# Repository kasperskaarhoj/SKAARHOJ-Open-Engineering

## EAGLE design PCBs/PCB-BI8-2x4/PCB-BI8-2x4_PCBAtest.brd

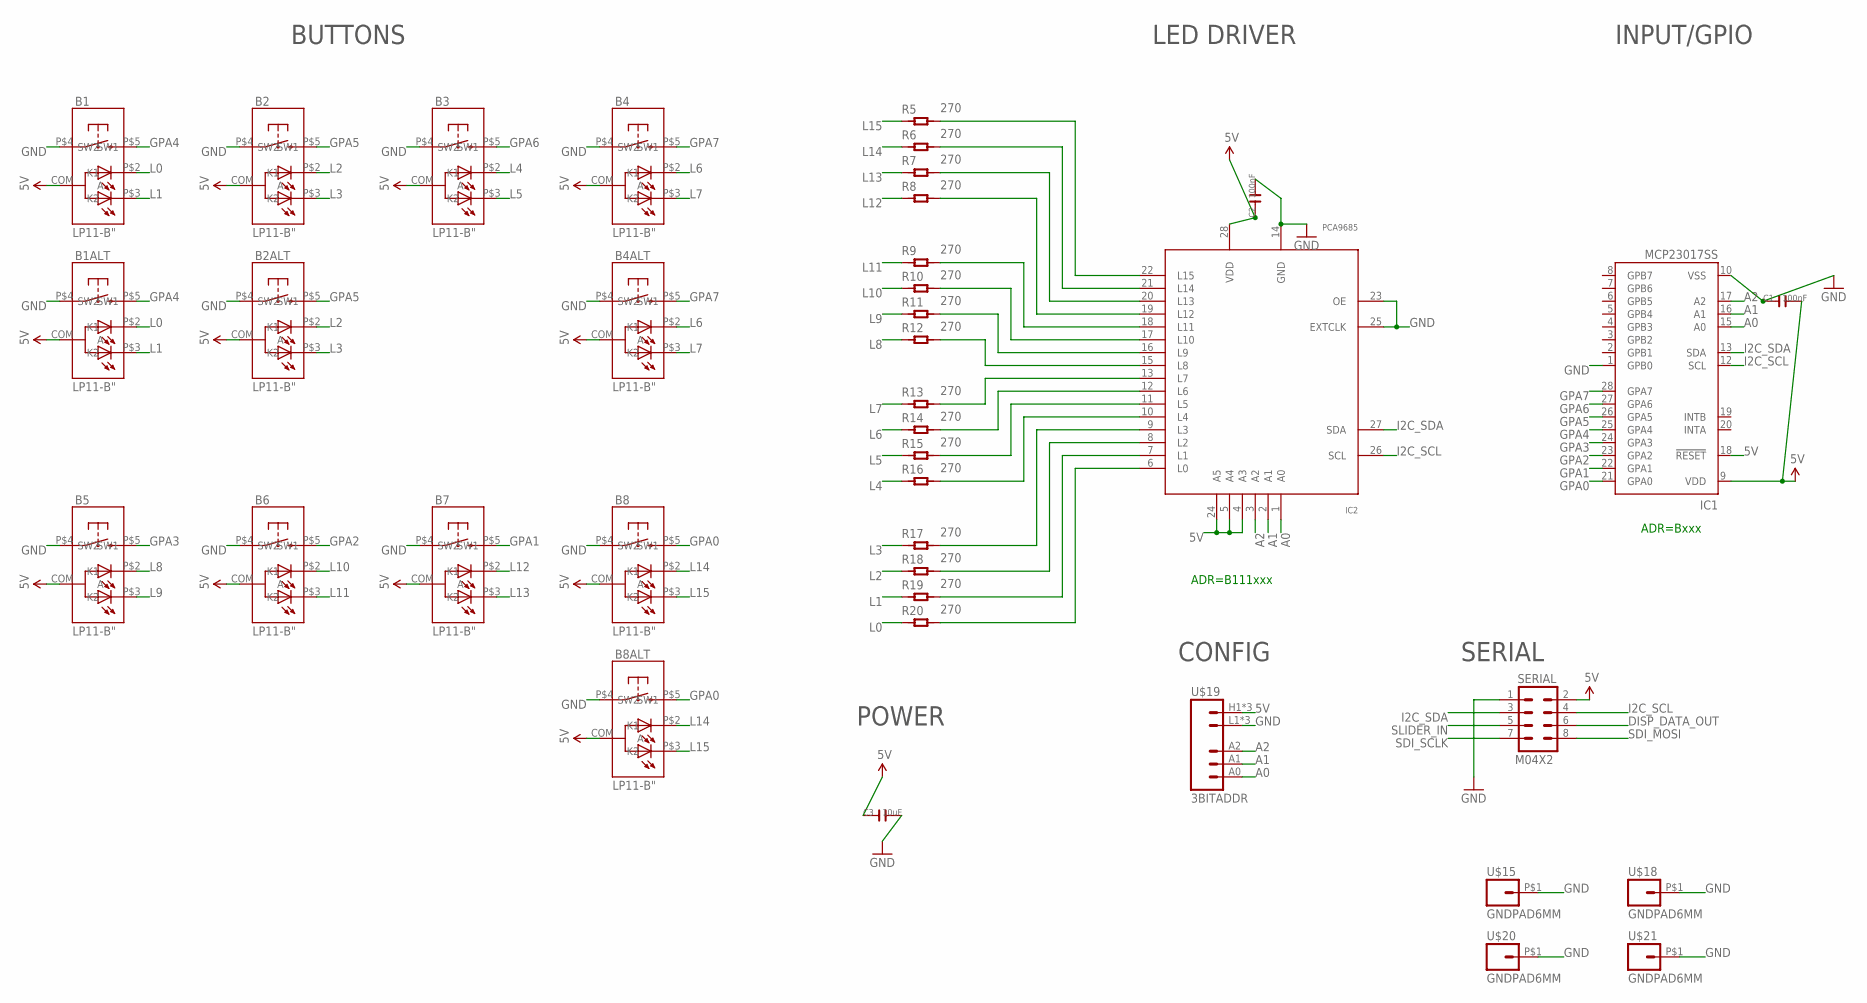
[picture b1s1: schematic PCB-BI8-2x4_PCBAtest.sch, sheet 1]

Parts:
B1, B1ALT, B2, B2ALT, B3, B4, B4ALT, B5, B6, B7, B8, B8ALT: LP11-B"; LP11
C1, C2: 100nF; C0603
C3: 10uF; C0805
IC1: MCP23017SS; SSOP28; MPN MCP23017-E/SS
IC2: PCA9685; TSSOP28
R5, R6, R7, R8, R9, R10, R11, R12, R13, R14, R15, R16, R17, R18, R19, R20: 270; R0603
SERIAL: M04X2; 2X4
U$15, U$18, U$20, U$21: GNDPAD6MM; 3.2MMPAD6MM
U$19: 3BITADDR

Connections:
5V: B1.COM (A), B1ALT.COM (A), B2.COM (A), B2ALT.COM (A), B3.COM (A), B4.COM (A), B4ALT.COM (A), B5.COM (A), B6.COM (A), B7.COM (A), B8.COM (A), B8ALT.COM (A), C1.2, C2.1, C3.1, IC1.9 (VDD), IC1.18 (!RESET), IC2.4 (A3), IC2.5 (A4), IC2.24 (A5), IC2.28 (VDD), SERIAL.2, U$19.H1 (VCC), U$19.H2 (VCC), U$19.H3 (VCC)
A0: IC1.15 (A0), IC2.1 (A0), U$19.A0
A1: IC1.16 (A1), IC2.2 (A1), U$19.A1
A2: IC1.17 (A2), IC2.3 (A2), U$19.A2
DISP_DATA_OUT: SERIAL.6
GND: B1.P$4 (SW1), B1ALT.P$4 (SW1), B2.P$4 (SW1), B2ALT.P$4 (SW1), B3.P$4 (SW1), B4.P$4 (SW1), B4ALT.P$4 (SW1), B5.P$4 (SW1), B6.P$4 (SW1), B7.P$4 (SW1), B8.P$4 (SW1), B8ALT.P$4 (SW1), C1.1, C2.2, C3.2, IC1.1 (GPB0), IC1.10 (VSS), IC2.14 (GND), IC2.23 (OE), IC2.25 (EXTCLK), SERIAL.1, U$15.P$1, U$18.P$1, U$19.L1 (GND), U$19.L2 (GND), U$19.L3 (GND), U$20.P$1, U$21.P$1
GPA0: B8.P$5 (SW2), B8ALT.P$5 (SW2), IC1.21 (GPA0)
GPA1: B7.P$5 (SW2), IC1.22 (GPA1)
GPA2: B6.P$5 (SW2), IC1.23 (GPA2)
GPA3: B5.P$5 (SW2), IC1.24 (GPA3)
GPA4: B1.P$5 (SW2), B1ALT.P$5 (SW2), IC1.25 (GPA4)
GPA5: B2.P$5 (SW2), B2ALT.P$5 (SW2), IC1.26 (GPA5)
GPA6: B3.P$5 (SW2), IC1.27 (GPA6)
GPA7: B4.P$5 (SW2), B4ALT.P$5 (SW2), IC1.28 (GPA7)
I2C_SCL: IC1.12 (SCL), IC2.26 (SCL), SERIAL.4
I2C_SDA: IC1.13 (SDA), IC2.27 (SDA), SERIAL.3
L0: B1.P$2 (K1), B1ALT.P$2 (K1), R20.1
L1: B1.P$3 (K2), B1ALT.P$3 (K2), R19.1
L2: B2.P$2 (K1), B2ALT.P$2 (K1), R18.1
L3: B2.P$3 (K2), B2ALT.P$3 (K2), R17.1
L4: B3.P$2 (K1), R16.1
L5: B3.P$3 (K2), R15.1
L6: B4.P$2 (K1), B4ALT.P$2 (K1), R14.1
L7: B4.P$3 (K2), B4ALT.P$3 (K2), R13.1
L8: B5.P$2 (K1), R12.1
L9: B5.P$3 (K2), R11.1
L10: B6.P$2 (K1), R10.1
L11: B6.P$3 (K2), R9.1
L12: B7.P$2 (K1), R8.1
L13: B7.P$3 (K2), R7.1
L14: B8.P$2 (K1), B8ALT.P$2 (K1), R6.1
L15: B8.P$3 (K2), B8ALT.P$3 (K2), R5.1
unnamed: IC2.13 (L7), R13.2
unnamed: IC2.12 (L6), R14.2
unnamed: IC2.11 (L5), R15.2
unnamed: IC2.10 (L4), R16.2
unnamed: IC2.9 (L3), R17.2
unnamed: IC2.8 (L2), R18.2
unnamed: IC2.7 (L1), R19.2
unnamed: IC2.6 (L0), R20.2
unnamed: IC2.15 (L8), R12.2
unnamed: IC2.16 (L9), R11.2
unnamed: IC2.17 (L10), R10.2
unnamed: IC2.18 (L11), R9.2
unnamed: IC2.19 (L12), R8.2
unnamed: IC2.20 (L13), R7.2
unnamed: IC2.21 (L14), R6.2
unnamed: IC2.22 (L15), R5.2
SDI_MOSI: SERIAL.8
SDI_SCLK: SERIAL.7
SLIDER_IN: SERIAL.5

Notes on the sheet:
ADR=B111xxx
ADR=Bxxx
BUTTONS
LED DRIVER
INPUT/GPIO
POWER
SERIAL
CONFIG

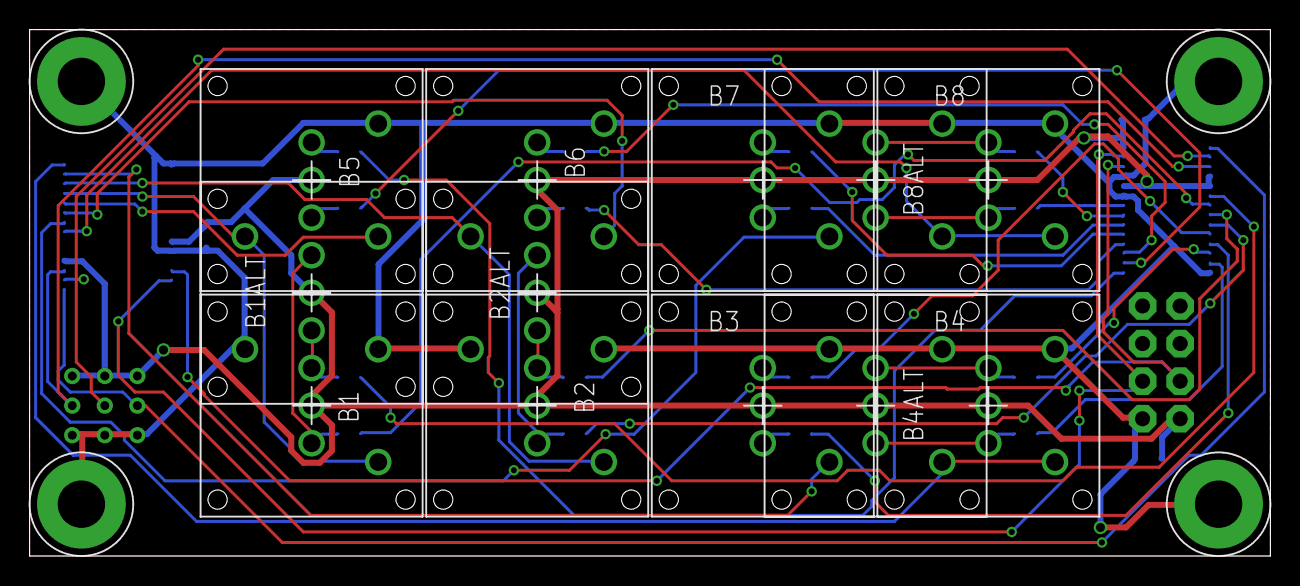
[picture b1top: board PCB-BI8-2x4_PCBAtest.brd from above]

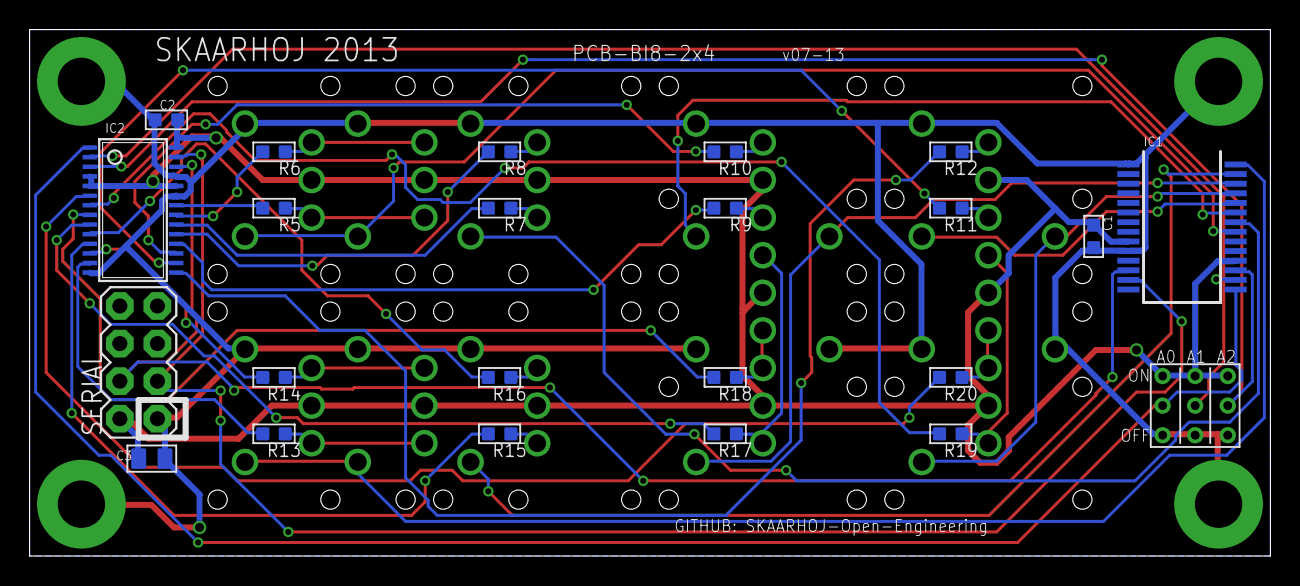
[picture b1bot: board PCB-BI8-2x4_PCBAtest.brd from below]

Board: 2 copper layers, 83.8 x 35.6 mm, 39 parts (23 on the bottom side), 47 nets.

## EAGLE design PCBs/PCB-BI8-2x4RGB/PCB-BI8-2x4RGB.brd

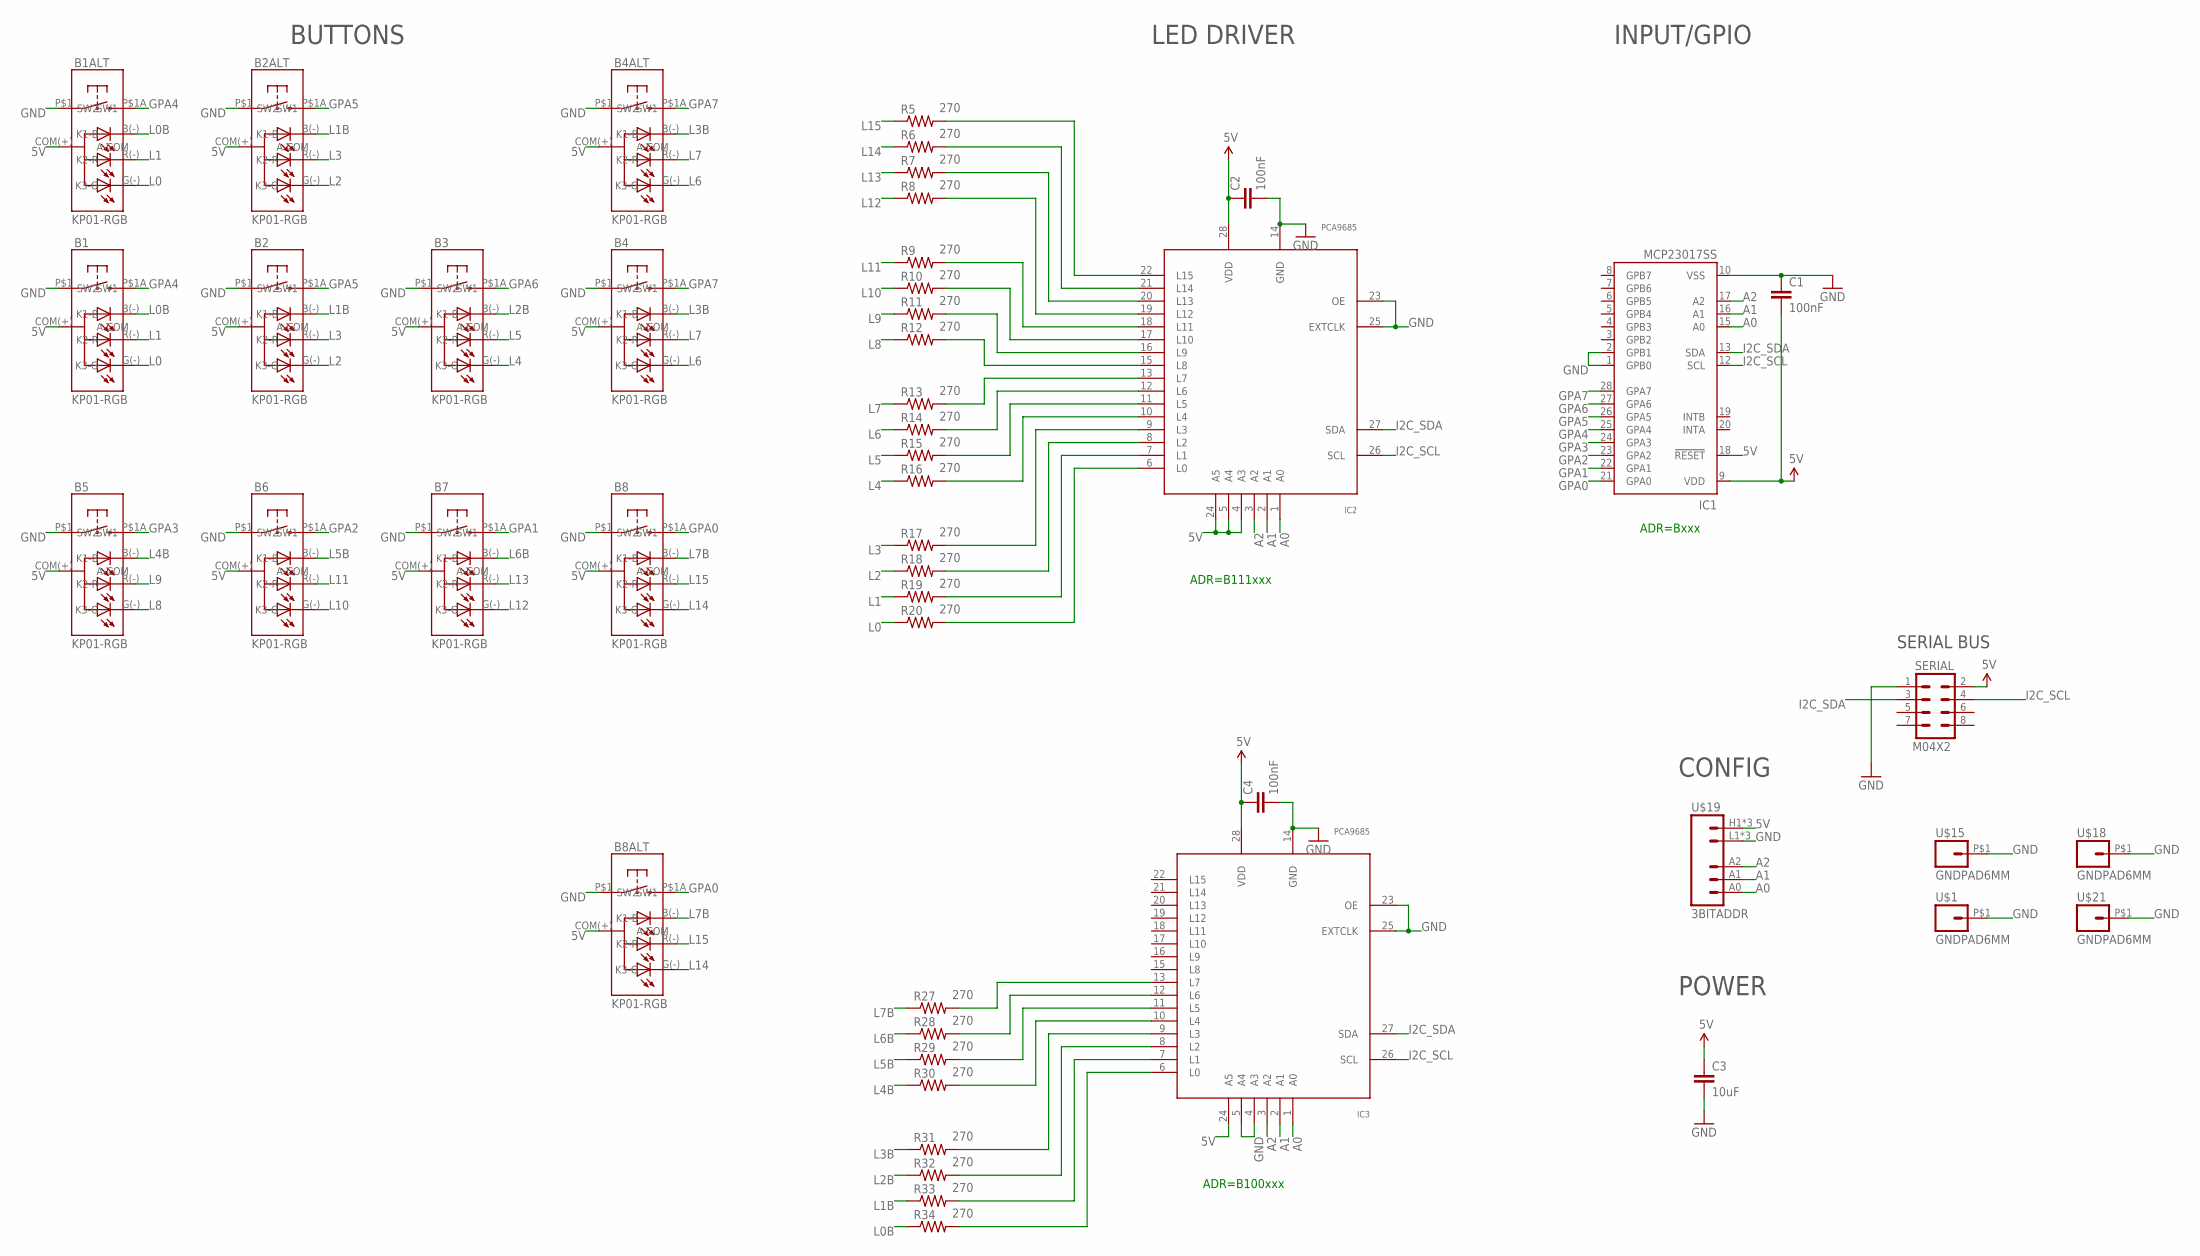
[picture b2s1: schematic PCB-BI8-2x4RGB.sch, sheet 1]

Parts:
B1, B1ALT, B2, B2ALT, B3, B4, B4ALT, B5, B6, B7, B8, B8ALT: KP01-RGB; NKK-KP01
C1, C2, C4: 100nF; 0603-CAP
C3: 10uF; 0805
IC1: MCP23017SS; SSOP28; MPN MCP23017-E/SS
IC2, IC3: PCA9685; TSSOP28
R5, R6, R7, R8, R9, R10, R11, R12, R13, R14, R15, R16, R17, R18, R19, R20, R27, R28, R29, R30, R31, R32, R33, R34: 270; 0603-RES
SERIAL: M04X2; 2X4
U$1, U$15, U$18, U$21: GNDPAD6MM; 3.2MMPAD6MM
U$19: 3BITADDR

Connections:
5V: B1.COM(+) (A-COM), B1ALT.COM(+) (A-COM), B2.COM(+) (A-COM), B2ALT.COM(+) (A-COM), B3.COM(+) (A-COM), B4.COM(+) (A-COM), B4ALT.COM(+) (A-COM), B5.COM(+) (A-COM), B6.COM(+) (A-COM), B7.COM(+) (A-COM), B8.COM(+) (A-COM), B8ALT.COM(+) (A-COM), C1.2, C2.1, C3.1, C4.1, IC1.9 (VDD), IC1.18 (!RESET), IC2.4 (A3), IC2.5 (A4), IC2.24 (A5), IC2.28 (VDD), IC3.24 (A5), IC3.28 (VDD), SERIAL.2, U$19.H1 (VCC), U$19.H2 (VCC), U$19.H3 (VCC)
A0: IC1.15 (A0), IC2.1 (A0), IC3.1 (A0), U$19.A0
A1: IC1.16 (A1), IC2.2 (A1), IC3.2 (A1), U$19.A1
A2: IC1.17 (A2), IC2.3 (A2), IC3.3 (A2), U$19.A2
GND: B1.P$1 (SW1), B1ALT.P$1 (SW1), B2.P$1 (SW1), B2ALT.P$1 (SW1), B3.P$1 (SW1), B4.P$1 (SW1), B4ALT.P$1 (SW1), B5.P$1 (SW1), B6.P$1 (SW1), B7.P$1 (SW1), B8.P$1 (SW1), B8ALT.P$1 (SW1), C1.1, C2.2, C3.2, C4.2, IC1.1 (GPB0), IC1.2 (GPB1), IC1.10 (VSS), IC2.14 (GND), IC2.23 (OE), IC2.25 (EXTCLK), IC3.4 (A3), IC3.5 (A4), IC3.14 (GND), IC3.23 (OE), IC3.25 (EXTCLK), SERIAL.1, U$1.P$1, U$15.P$1, U$18.P$1, U$19.L1 (GND), U$19.L2 (GND), U$19.L3 (GND), U$21.P$1
GPA0: B8.P$1A (SW2), B8ALT.P$1A (SW2), IC1.21 (GPA0)
GPA1: B7.P$1A (SW2), IC1.22 (GPA1)
GPA2: B6.P$1A (SW2), IC1.23 (GPA2)
GPA3: B5.P$1A (SW2), IC1.24 (GPA3)
GPA4: B1.P$1A (SW2), B1ALT.P$1A (SW2), IC1.25 (GPA4)
GPA5: B2.P$1A (SW2), B2ALT.P$1A (SW2), IC1.26 (GPA5)
GPA6: B3.P$1A (SW2), IC1.27 (GPA6)
GPA7: B4.P$1A (SW2), B4ALT.P$1A (SW2), IC1.28 (GPA7)
I2C_SCL: IC1.12 (SCL), IC2.26 (SCL), IC3.26 (SCL), SERIAL.4
I2C_SDA: IC1.13 (SDA), IC2.27 (SDA), IC3.27 (SDA), SERIAL.3
L0: B1.G(-) (K3-G), B1ALT.G(-) (K3-G), R20.1
L0B: B1.B(-) (K1-B), B1ALT.B(-) (K1-B), R34.1
L1: B1.R(-) (K2-R), B1ALT.R(-) (K2-R), R19.1
L1B: B2.B(-) (K1-B), B2ALT.B(-) (K1-B), R33.1
L2: B2.G(-) (K3-G), B2ALT.G(-) (K3-G), R18.1
L2B: B3.B(-) (K1-B), R32.1
L3: B2.R(-) (K2-R), B2ALT.R(-) (K2-R), R17.1
L3B: B4.B(-) (K1-B), B4ALT.B(-) (K1-B), R31.1
L4: B3.G(-) (K3-G), R16.1
L4B: B5.B(-) (K1-B), R30.1
L5: B3.R(-) (K2-R), R15.1
L5B: B6.B(-) (K1-B), R29.1
L6: B4.G(-) (K3-G), B4ALT.G(-) (K3-G), R14.1
L6B: B7.B(-) (K1-B), R28.1
L7: B4.R(-) (K2-R), B4ALT.R(-) (K2-R), R13.1
L7B: B8.B(-) (K1-B), B8ALT.B(-) (K1-B), R27.1
L8: B5.G(-) (K3-G), R12.1
L9: B5.R(-) (K2-R), R11.1
L10: B6.G(-) (K3-G), R10.1
L11: B6.R(-) (K2-R), R9.1
L12: B7.G(-) (K3-G), R8.1
L13: B7.R(-) (K2-R), R7.1
L14: B8.G(-) (K3-G), B8ALT.G(-) (K3-G), R6.1
L15: B8.R(-) (K2-R), B8ALT.R(-) (K2-R), R5.1
unnamed: IC3.13 (L7), R27.2
unnamed: IC3.12 (L6), R28.2
unnamed: IC2.13 (L7), R13.2
unnamed: IC2.12 (L6), R14.2
unnamed: IC3.11 (L5), R29.2
unnamed: IC2.11 (L5), R15.2
unnamed: IC2.10 (L4), R16.2
unnamed: IC2.9 (L3), R17.2
unnamed: IC2.8 (L2), R18.2
unnamed: IC2.7 (L1), R19.2
unnamed: IC3.10 (L4), R30.2
unnamed: IC3.9 (L3), R31.2
unnamed: IC3.8 (L2), R32.2
unnamed: IC3.7 (L1), R33.2
unnamed: IC3.6 (L0), R34.2
unnamed: IC2.6 (L0), R20.2
unnamed: IC2.15 (L8), R12.2
unnamed: IC2.16 (L9), R11.2
unnamed: IC2.17 (L10), R10.2
unnamed: IC2.18 (L11), R9.2
unnamed: IC2.19 (L12), R8.2
unnamed: IC2.20 (L13), R7.2
unnamed: IC2.21 (L14), R6.2
unnamed: IC2.22 (L15), R5.2

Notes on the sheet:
SERIAL BUS
ADR=B111xxx
ADR=Bxxx
BUTTONS
LED DRIVER
INPUT/GPIO
POWER
ADR=B100xxx
CONFIG

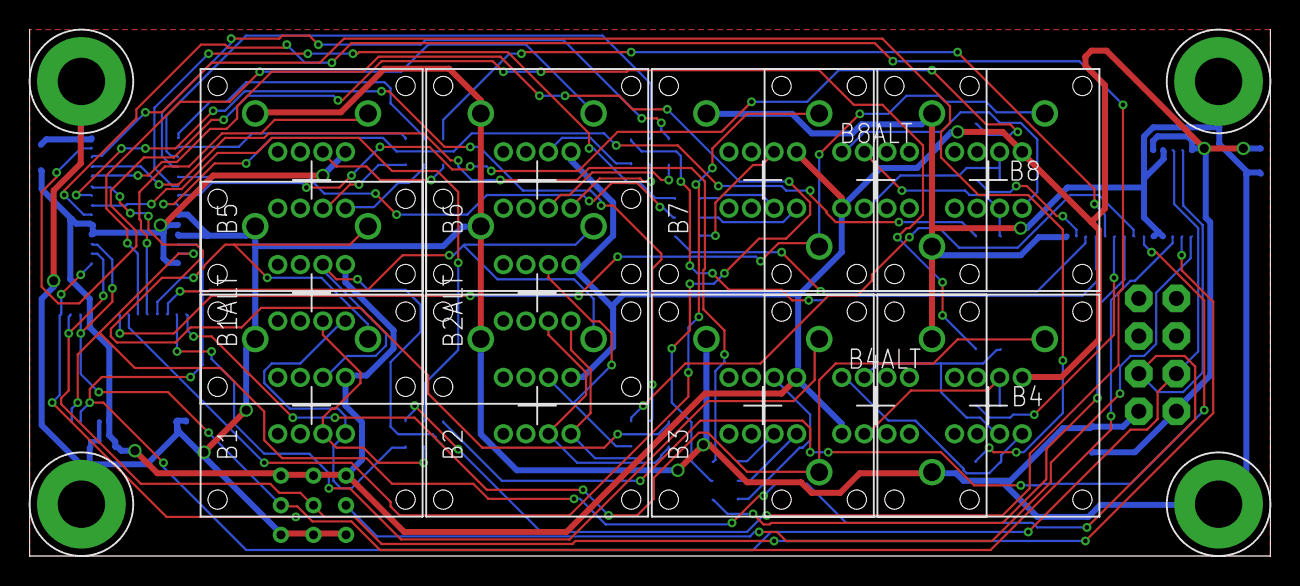
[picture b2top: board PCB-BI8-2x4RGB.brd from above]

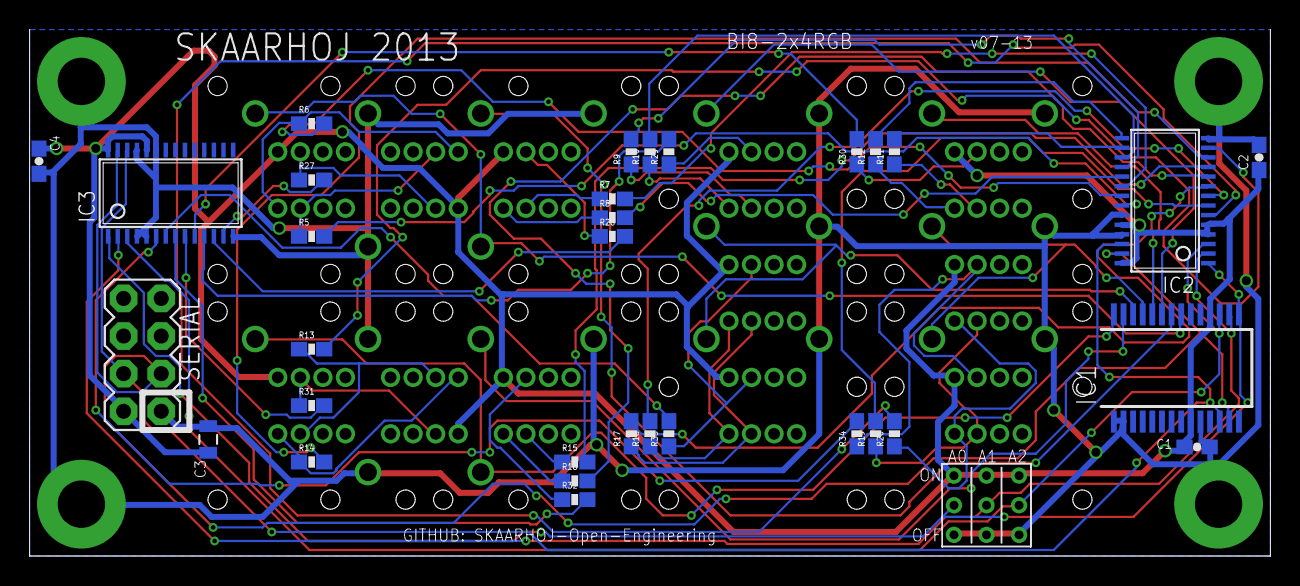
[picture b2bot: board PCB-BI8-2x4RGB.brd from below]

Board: 2 copper layers, 83.8 x 35.6 mm, 49 parts (33 on the bottom side), 63 nets.

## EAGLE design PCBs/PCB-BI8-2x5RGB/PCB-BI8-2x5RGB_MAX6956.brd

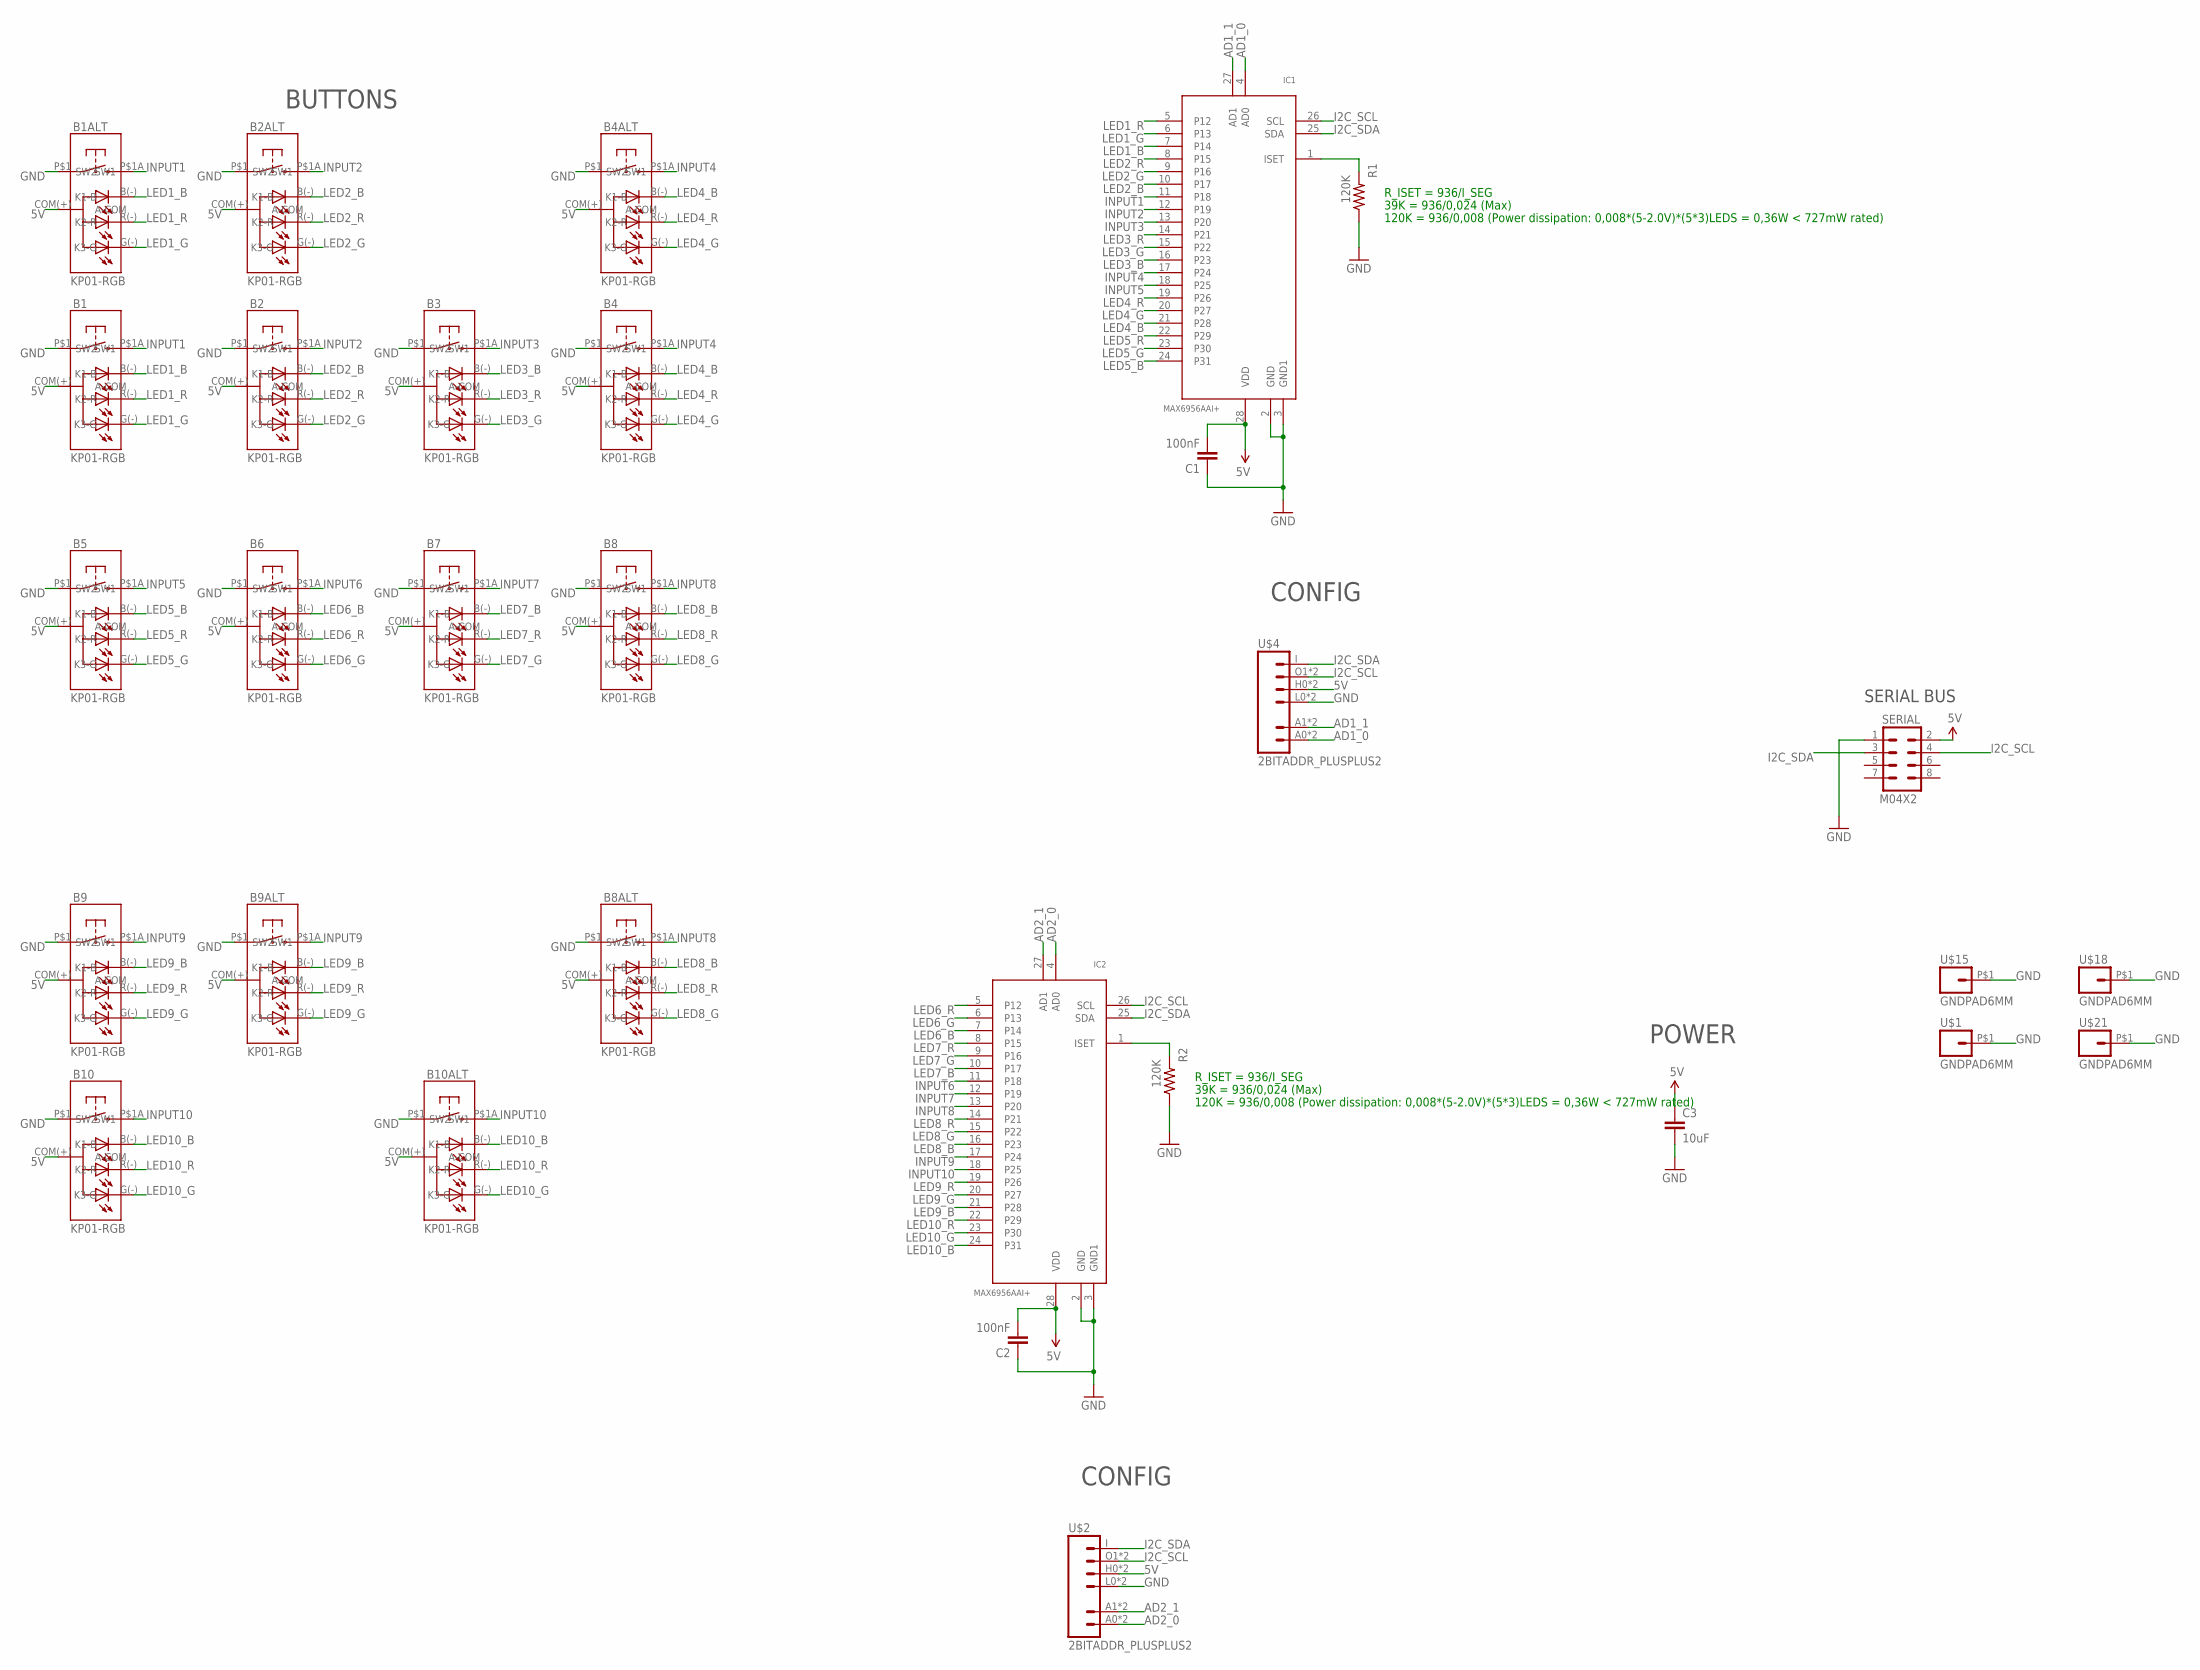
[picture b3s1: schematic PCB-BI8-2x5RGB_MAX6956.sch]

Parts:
B1, B1ALT, B2, B2ALT, B3, B4, B4ALT, B5, B6, B7, B8, B8ALT, B9, B9ALT, B10, B10ALT: KP01-RGB; NKK-KP01
C1, C2: 100nF; 0603-CAP
C3: 10uF; 0805
IC1, IC2: MAX6956AAI+; SSOP28
R1, R2: 120K; 0603-RES
SERIAL: M04X2; 2X4
U$1, U$15, U$18, U$21: GNDPAD6MM; 3.2MMPAD6MM
U$2, U$4: 2BITADDR_PLUSPLUS2; 2BITADDR_SMALL_PLUS2

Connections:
5V: B1.COM(+) (A-COM), B1ALT.COM(+) (A-COM), B2.COM(+) (A-COM), B2ALT.COM(+) (A-COM), B3.COM(+) (A-COM), B4.COM(+) (A-COM), B4ALT.COM(+) (A-COM), B5.COM(+) (A-COM), B6.COM(+) (A-COM), B7.COM(+) (A-COM), B8.COM(+) (A-COM), B8ALT.COM(+) (A-COM), B9.COM(+) (A-COM), B9ALT.COM(+) (A-COM), B10.COM(+) (A-COM), B10ALT.COM(+) (A-COM), C1.2, C2.2, C3.1, IC1.28 (VDD), IC2.28 (VDD), SERIAL.2, U$2.H0 (VCC), U$2.H1 (VCC), U$4.H0 (VCC), U$4.H1 (VCC)
AD1_0: IC1.4 (AD0), U$4.A0 (A1), U$4.AS0 (A1)
AD1_1: IC1.27 (AD1), U$4.A1 (A2), U$4.AS1 (A2)
AD2_0: IC2.4 (AD0), U$2.A0 (A1), U$2.AS0 (A1)
AD2_1: IC2.27 (AD1), U$2.A1 (A2), U$2.AS1 (A2)
GND: B1.P$1 (SW1), B1ALT.P$1 (SW1), B2.P$1 (SW1), B2ALT.P$1 (SW1), B3.P$1 (SW1), B4.P$1 (SW1), B4ALT.P$1 (SW1), B5.P$1 (SW1), B6.P$1 (SW1), B7.P$1 (SW1), B8.P$1 (SW1), B8ALT.P$1 (SW1), B9.P$1 (SW1), B9ALT.P$1 (SW1), B10.P$1 (SW1), B10ALT.P$1 (SW1), C1.1, C2.1, C3.2, IC1.2 (GND), IC1.3 (GND1), IC2.2 (GND), IC2.3 (GND1), R1.1, R2.1, SERIAL.1, U$1.P$1, U$2.L0 (GND), U$2.L1 (GND), U$4.L0 (GND), U$4.L1 (GND), U$15.P$1, U$18.P$1, U$21.P$1
I2C_SCL: IC1.26 (SCL), IC2.26 (SCL), SERIAL.4, U$2.O1 (3), U$2.O2 (3), U$4.O1 (3), U$4.O2 (3)
I2C_SDA: IC1.25 (SDA), IC2.25 (SDA), SERIAL.3, U$2.I (4), U$4.I (4)
INPUT1: B1.P$1A (SW2), B1ALT.P$1A (SW2), IC1.11 (P18)
INPUT2: B2.P$1A (SW2), B2ALT.P$1A (SW2), IC1.12 (P19)
INPUT3: B3.P$1A (SW2), IC1.13 (P20)
INPUT4: B4.P$1A (SW2), B4ALT.P$1A (SW2), IC1.17 (P24)
INPUT5: B5.P$1A (SW2), IC1.18 (P25)
INPUT6: B6.P$1A (SW2), IC2.11 (P18)
INPUT7: B7.P$1A (SW2), IC2.12 (P19)
INPUT8: B8.P$1A (SW2), B8ALT.P$1A (SW2), IC2.13 (P20)
INPUT9: B9.P$1A (SW2), B9ALT.P$1A (SW2), IC2.17 (P24)
INPUT10: B10.P$1A (SW2), B10ALT.P$1A (SW2), IC2.18 (P25)
LED1_B: B1.B(-) (K1-B), B1ALT.B(-) (K1-B), IC1.7 (P14)
LED1_G: B1.G(-) (K3-G), B1ALT.G(-) (K3-G), IC1.6 (P13)
LED1_R: B1.R(-) (K2-R), B1ALT.R(-) (K2-R), IC1.5 (P12)
LED2_B: B2.B(-) (K1-B), B2ALT.B(-) (K1-B), IC1.10 (P17)
LED2_G: B2.G(-) (K3-G), B2ALT.G(-) (K3-G), IC1.9 (P16)
LED2_R: B2.R(-) (K2-R), B2ALT.R(-) (K2-R), IC1.8 (P15)
LED3_B: B3.B(-) (K1-B), IC1.16 (P23)
LED3_G: B3.G(-) (K3-G), IC1.15 (P22)
LED3_R: B3.R(-) (K2-R), IC1.14 (P21)
LED4_B: B4.B(-) (K1-B), B4ALT.B(-) (K1-B), IC1.21 (P28)
LED4_G: B4.G(-) (K3-G), B4ALT.G(-) (K3-G), IC1.20 (P27)
LED4_R: B4.R(-) (K2-R), B4ALT.R(-) (K2-R), IC1.19 (P26)
LED5_B: B5.B(-) (K1-B), IC1.24 (P31)
LED5_G: B5.G(-) (K3-G), IC1.23 (P30)
LED5_R: B5.R(-) (K2-R), IC1.22 (P29)
LED6_B: B6.B(-) (K1-B), IC2.7 (P14)
LED6_G: B6.G(-) (K3-G), IC2.6 (P13)
LED6_R: B6.R(-) (K2-R), IC2.5 (P12)
LED7_B: B7.B(-) (K1-B), IC2.10 (P17)
LED7_G: B7.G(-) (K3-G), IC2.9 (P16)
LED7_R: B7.R(-) (K2-R), IC2.8 (P15)
LED8_B: B8.B(-) (K1-B), B8ALT.B(-) (K1-B), IC2.16 (P23)
LED8_G: B8.G(-) (K3-G), B8ALT.G(-) (K3-G), IC2.15 (P22)
LED8_R: B8.R(-) (K2-R), B8ALT.R(-) (K2-R), IC2.14 (P21)
LED9_B: B9.B(-) (K1-B), B9ALT.B(-) (K1-B), IC2.21 (P28)
LED9_G: B9.G(-) (K3-G), B9ALT.G(-) (K3-G), IC2.20 (P27)
LED9_R: B9.R(-) (K2-R), B9ALT.R(-) (K2-R), IC2.19 (P26)
LED10_B: B10.B(-) (K1-B), B10ALT.B(-) (K1-B), IC2.24 (P31)
LED10_G: B10.G(-) (K3-G), B10ALT.G(-) (K3-G), IC2.23 (P30)
LED10_R: B10.R(-) (K2-R), B10ALT.R(-) (K2-R), IC2.22 (P29)
unnamed: IC2.1 (ISET), R2.2
unnamed: IC1.1 (ISET), R1.2

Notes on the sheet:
SERIAL BUS
BUTTONS
POWER
CONFIG
R_ISET = 936/I_SEG
39K = 936/0,024 (Max)
120K = 936/0,008 (Power dissipation: 0,008*(5-2.0V)*(5*3)LEDS = 0,36W < 727mW rated)

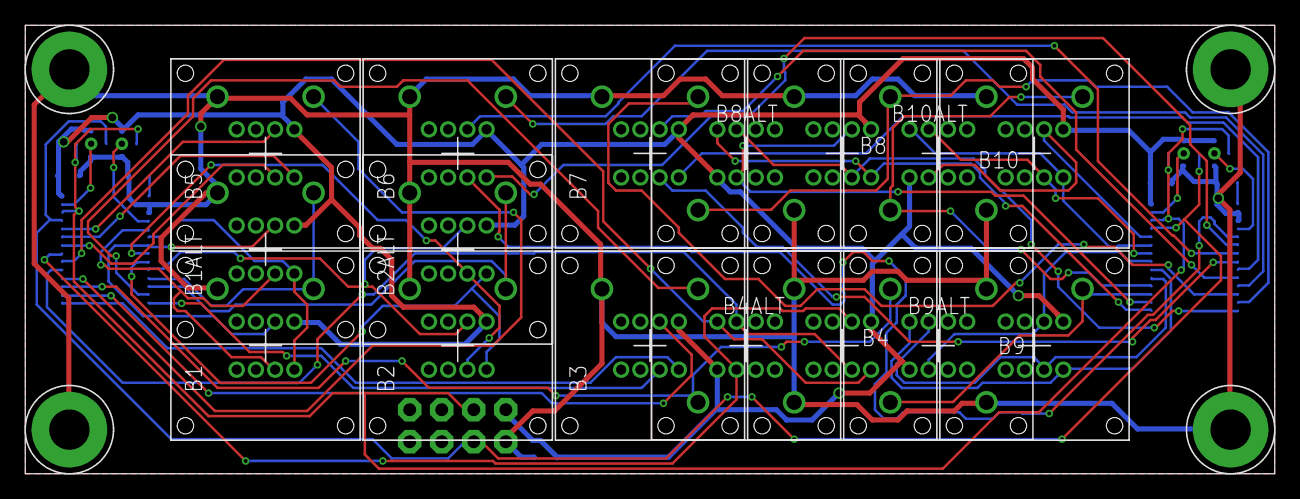
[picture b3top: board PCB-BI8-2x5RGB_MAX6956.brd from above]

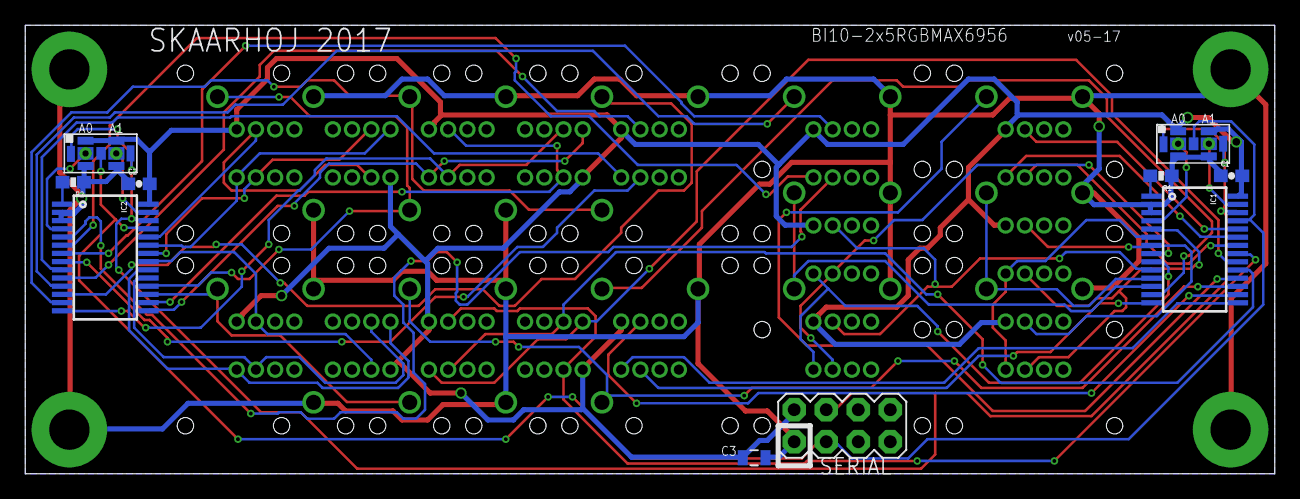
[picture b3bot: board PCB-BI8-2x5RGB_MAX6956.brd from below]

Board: 2 copper layers, 99.1 x 35.6 mm, 30 parts (10 on the bottom side), 50 nets.

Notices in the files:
parts and their libraries:
SparkFun: Licensing: CC v3.0 Share-Alike You are welcome to use this library for commercial purposes.
